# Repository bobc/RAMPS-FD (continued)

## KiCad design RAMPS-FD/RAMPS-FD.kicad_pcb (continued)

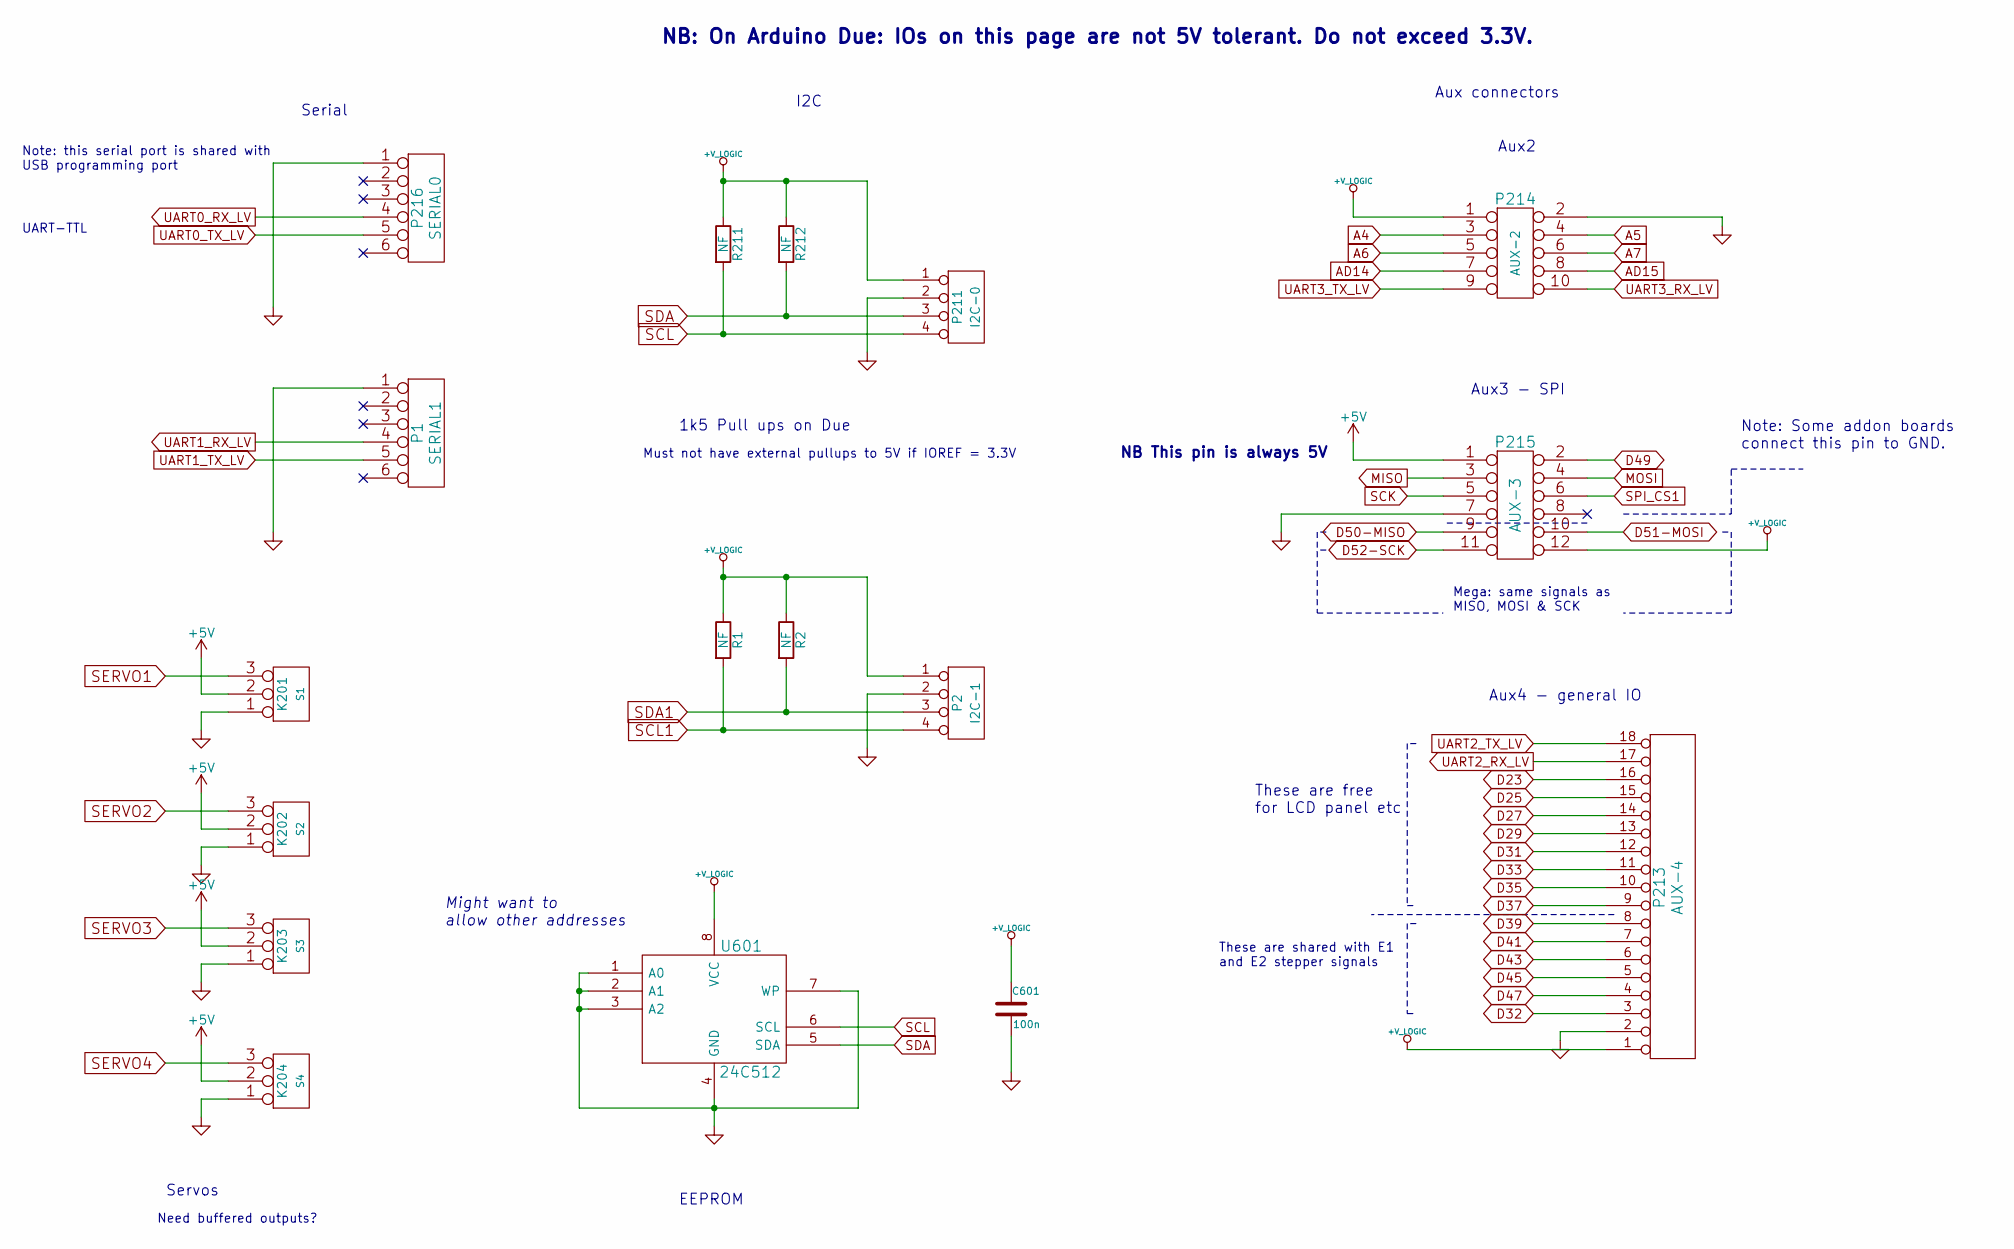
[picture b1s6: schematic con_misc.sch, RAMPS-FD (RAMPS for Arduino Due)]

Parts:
C601: 100n; C_0603
K201: S1; Pin_Header_Straight_1x03_Pitch2.54mm
K202: S2; Pin_Header_Straight_1x03_Pitch2.54mm
K203: S3; Pin_Header_Straight_1x03_Pitch2.54mm
K204: S4; Pin_Header_Straight_1x03_Pitch2.54mm
P1: SERIAL1; Pin_Header_Straight_1x06_Pitch2.54mm
P2: I2C-1; Pin_Header_Straight_1x04_Pitch2.54mm
P211: I2C-0; Pin_Header_Straight_1x04_Pitch2.54mm
P213: AUX-4; Pin_Header_Straight_1x18_Pitch2.54mm
P214: AUX-2; PIN_ARRAY_5x2_RMC
P215: AUX-3; PIN_ARRAY_6x2_RMC
P216: SERIAL0; Pin_Header_Straight_1x06_Pitch2.54mm
R1, R2, R211, R212: NF; R_0603
U601: 24C512; SO8E

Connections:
+5V: K201.2 (PM), K202.2 (PM), K203.2 (PM), K204.2 (PM), P215.1; also elsewhere on the board
+V_LOGIC: C601.1, P2.1, P211.1, P213.1, P214.1, P215.12, R1.1, R2.1, R211.1, R212.1, U601.8 (VCC); also elsewhere on the board
A4: P214.3; also elsewhere on the board
A5: P214.4; also elsewhere on the board
A6: P214.5; also elsewhere on the board
A7: P214.6; also elsewhere on the board
AD14: P214.7; also elsewhere on the board
AD15: P214.8; also elsewhere on the board
D23: P213.16; also elsewhere on the board
D25: P213.15; also elsewhere on the board
D27: P213.14; also elsewhere on the board
D29: P213.13; also elsewhere on the board
D31: P213.12; also elsewhere on the board
D32: P213.3; also elsewhere on the board
D33: P213.11; also elsewhere on the board
D35: P213.10; also elsewhere on the board
D37: P213.9; also elsewhere on the board
D39: P213.8; also elsewhere on the board
D41: P213.7; also elsewhere on the board
D43: P213.6; also elsewhere on the board
D45: P213.5; also elsewhere on the board
D47: P213.4; also elsewhere on the board
D49: P215.2; also elsewhere on the board
D50-MISO: P215.9; also elsewhere on the board
D51-MOSI: P215.10; also elsewhere on the board
D52-SCK: P215.11; also elsewhere on the board
GND: C601.2, K201.1, K202.1, K203.1, K204.1, P1.1, P2.2, P211.2, P213.2, P214.2, P215.7, P216.1, U601.1 (A0), U601.2 (A1), U601.3 (A2), U601.4 (GND), U601.7 (WP); also elsewhere on the board
MISO: P215.3; also elsewhere on the board
MOSI: P215.4; also elsewhere on the board
SCK: P215.5; also elsewhere on the board
SCL: P211.4, R211.2, U601.6 (SCL); also elsewhere on the board
SCL1: P2.4, R1.2; also elsewhere on the board
SDA: P211.3, R212.2, U601.5 (SDA); also elsewhere on the board
SDA1: P2.3, R2.2; also elsewhere on the board
SERVO1: K201.3; also elsewhere on the board
SERVO2: K202.3; also elsewhere on the board
SERVO3: K203.3; also elsewhere on the board
SERVO4: K204.3; also elsewhere on the board
SPI_CS1: P215.6; also elsewhere on the board
UART0_RX_LV: P216.4; also elsewhere on the board
UART0_TX_LV: P216.5; also elsewhere on the board
UART1_RX_LV: P1.4; also elsewhere on the board
UART1_TX_LV: P1.5; also elsewhere on the board
UART2_RX_LV: P213.17; also elsewhere on the board
UART2_TX_LV: P213.18; also elsewhere on the board
UART3_RX_LV: P214.10; also elsewhere on the board
UART3_TX_LV: P214.9; also elsewhere on the board

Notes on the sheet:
Serial
UART-TTL
Need buffered outputs?
Must not have external pullups to 5V if IOREF = 3.3V
1k5 Pull ups on Due
Aux4 - general IO
Aux3 - SPI
Aux2
Aux connectors
Servos
I2C
NB: On Arduino Due: IOs on this page are not 5V tolerant. Do not exceed 3.3V.
Note: this serial port is shared with USB programming port
These are shared with E1 and E2 stepper signals
Mega: same signals as MISO, MOSI & SCK
NB This pin is always 5V
These are free for LCD panel etc
Note: Some addon boards connect this pin to GND.
EEPROM
Might want to allow other addresses

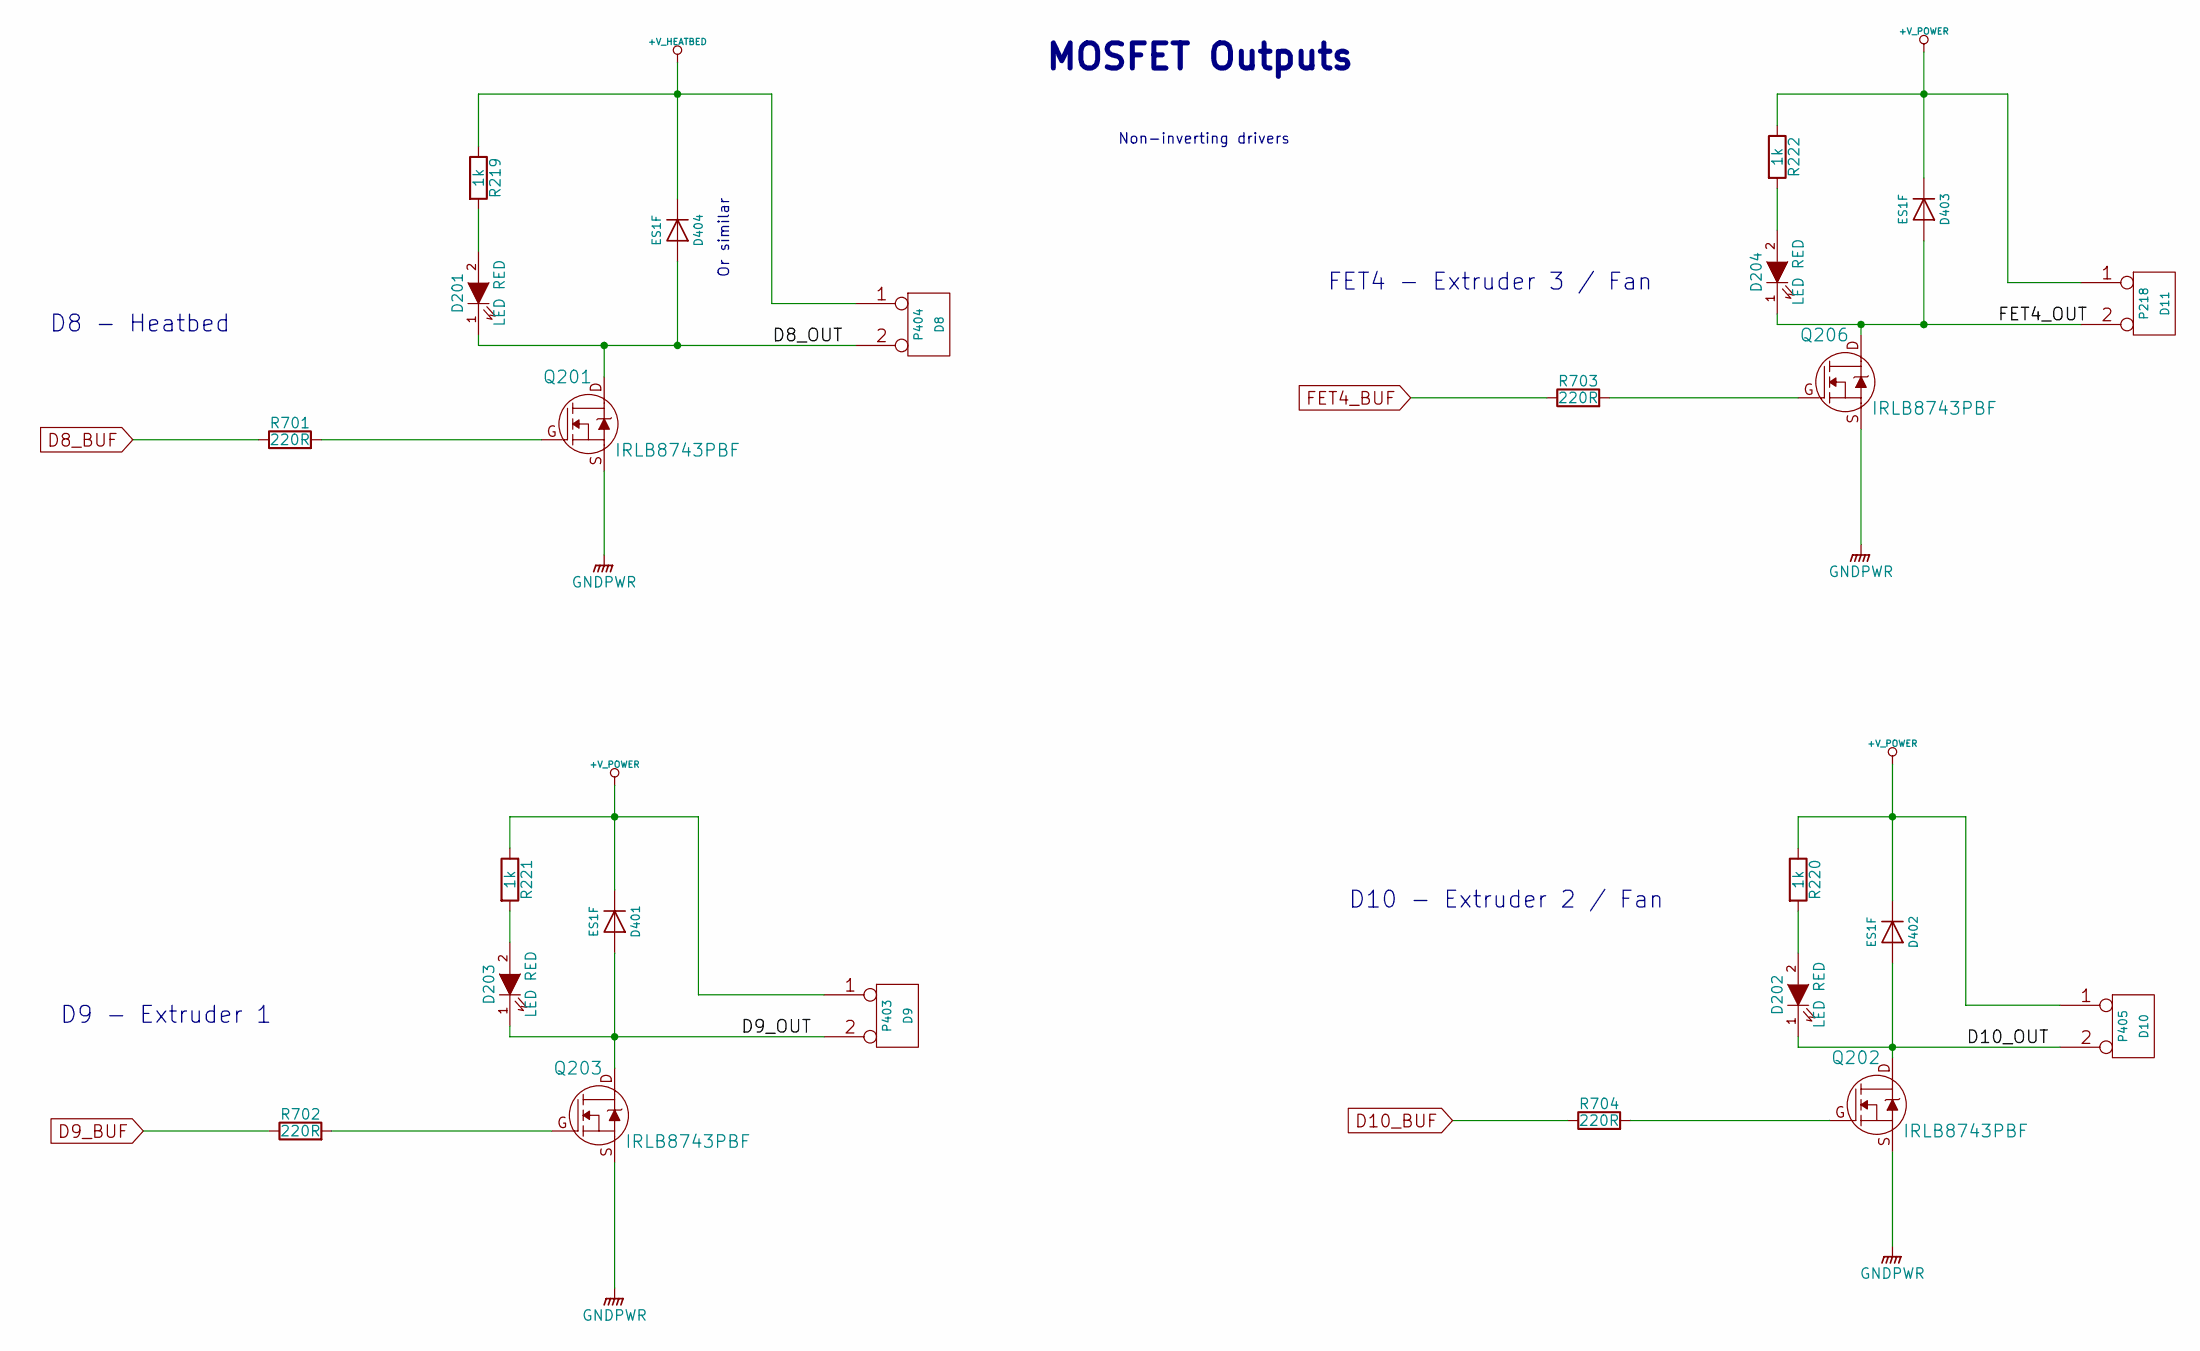
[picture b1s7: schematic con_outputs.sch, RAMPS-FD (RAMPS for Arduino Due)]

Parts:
D201, D202, D203, D204: LED RED; LED-0805_RED
D401, D402, D403, D404: ES1F; DO-214AC
P218: D11; RMC-pt_1,5-2-3,5-h
P403: D9; RMC-pt_1,5-2-3,5-h
P404: D8; mors_2p
P405: D10; RMC-pt_1,5-2-3,5-h
Q201, Q202, Q203, Q206: IRLB8743PBF; TO-220AB_IRF2804_RMC
R219, R220, R221, R222: 1k; R_0603
R701, R702, R703, R704: 220R; R_0603

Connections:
+V_HEATBED: D404.1 (K), P404.1, R219.1; also elsewhere on the board
+V_POWER: D401.1 (K), D402.1 (K), D403.1 (K), P218.1, P403.1, P405.1, R220.1, R221.1, R222.1; also elsewhere on the board
/Mosfet Outputs/D8_OUT: D201.1 (K), D404.2 (A), P404.2 (PM), Q201.D
/Mosfet Outputs/D9_OUT: D203.1 (K), D401.2 (A), P403.2 (PM), Q203.D
/Mosfet Outputs/D10_OUT: D202.1 (K), D402.2 (A), P405.2 (PM), Q202.D
/Mosfet Outputs/FET4_OUT: D204.1 (K), D403.2 (A), P218.2 (PM), Q206.D
D8_BUF: R701.1; also elsewhere on the board
D9_BUF: R702.1; also elsewhere on the board
D10_BUF: R704.1; also elsewhere on the board
FET4_BUF: R703.1; also elsewhere on the board
MOT_GND: Q201.S, Q202.S, Q203.S, Q206.S; also elsewhere on the board
unnamed: D201.2 (A), R219.2
unnamed: D202.2 (A), R220.2
unnamed: D203.2 (A), R221.2
unnamed: D204.2 (A), R222.2
unnamed: Q201.G, R701.2
unnamed: Q202.G, R704.2
unnamed: Q203.G, R702.2
unnamed: Q206.G, R703.2

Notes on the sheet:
FET4 - Extruder 3 / Fan
D10 - Extruder 2 / Fan
D9 - Extruder 1
D8 - Heatbed
Non-inverting drivers
MOSFET Outputs
Or similar

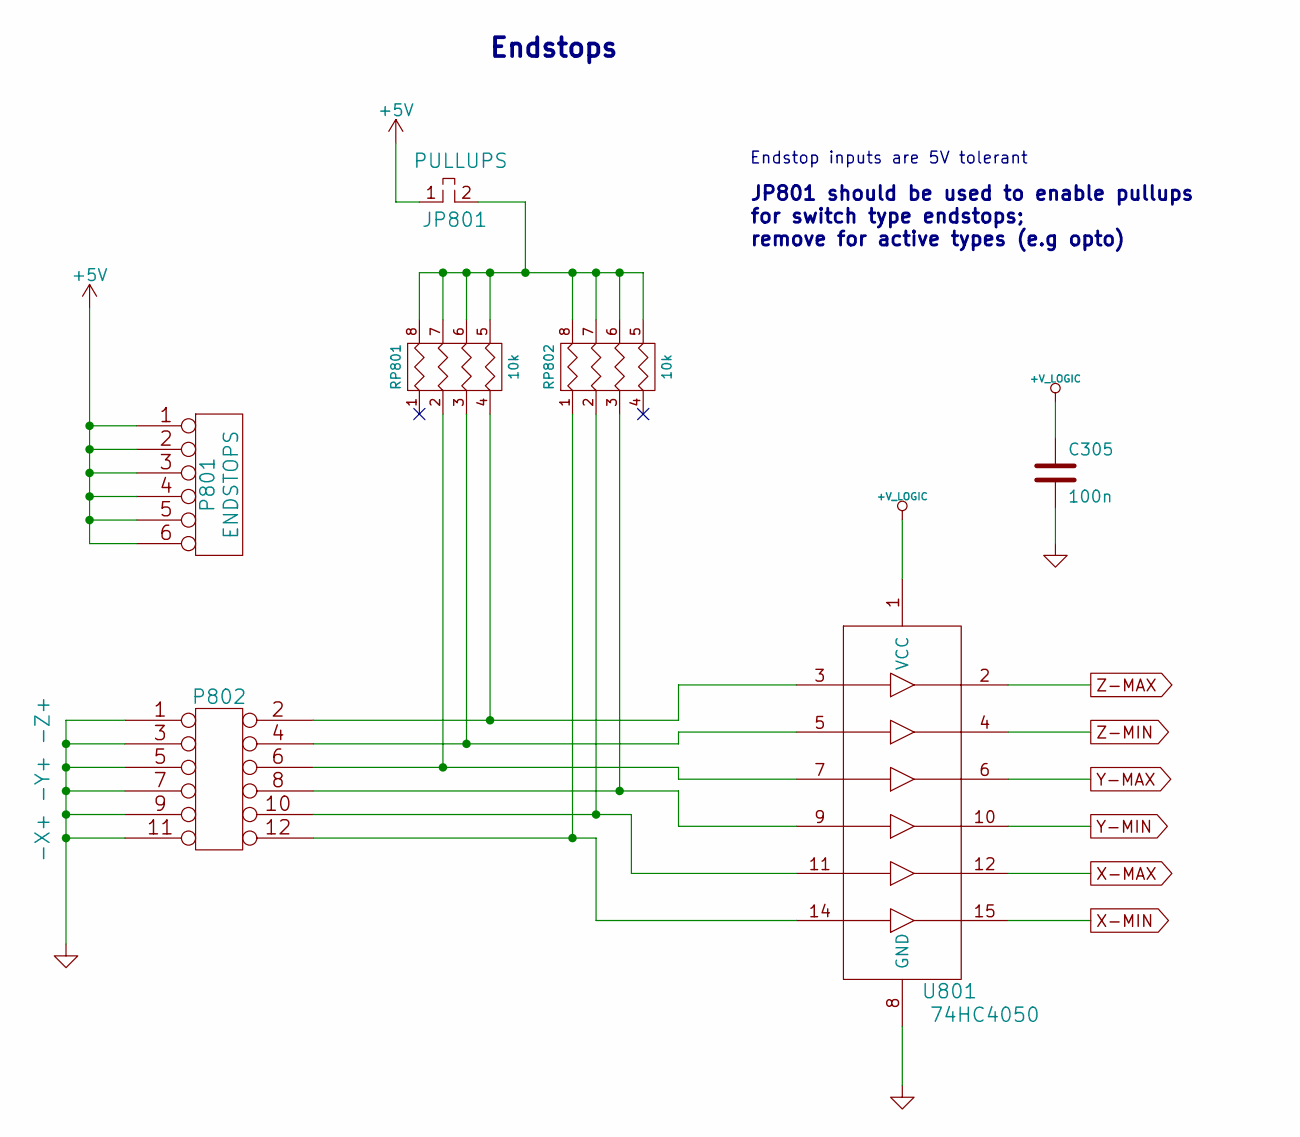
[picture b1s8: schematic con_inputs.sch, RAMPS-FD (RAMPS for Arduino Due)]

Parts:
C305: 100n; C_0603
JP801: PULLUPS; Pin_Header_Straight_1x02_Pitch2.54mm
P801: ENDSTOPS; Pin_Header_Straight_1x06_Pitch2.54mm
P802: -X+ -Y+ -Z+; Pin_Header_Straight_2x06_Pitch2.54mm
RP801, RP802: 10k; R_Cat16-4
U801: 74HC4050; TSSOP-16_4.4x5mm_Pitch0.65mm

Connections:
+5V: JP801.1, P801.1, P801.2, P801.3, P801.4, P801.5, P801.6; also elsewhere on the board
+V_LOGIC: C305.1, U801.1 (VCC); also elsewhere on the board
GND: C305.2, P802.1, P802.3, P802.5, P802.7, P802.9, P802.11, U801.8 (GND); also elsewhere on the board
unnamed: JP801.2, RP801.5 (R4), RP801.6 (R3), RP801.7 (R2), RP801.8 (R1), RP802.5 (R4), RP802.6 (R3), RP802.7 (R2), RP802.8 (R1)
unnamed: P802.2, RP801.4, U801.3
unnamed: P802.4, RP801.3, U801.5
unnamed: P802.6, RP801.2, U801.7
unnamed: P802.8, RP802.3, U801.9
unnamed: P802.10, RP802.2, U801.11
unnamed: P802.12, RP802.1, U801.14
X-MAX: U801.12; also elsewhere on the board
X-MIN: U801.15; also elsewhere on the board
Y-MAX: U801.6; also elsewhere on the board
Y-MIN: U801.10; also elsewhere on the board
Z-MAX: U801.2; also elsewhere on the board
Z-MIN: U801.4; also elsewhere on the board

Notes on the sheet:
Endstop inputs are 5V tolerant
Endstops
JP801 should be used to enable pullups for switch type endstops; remove for active types (e.g opto)

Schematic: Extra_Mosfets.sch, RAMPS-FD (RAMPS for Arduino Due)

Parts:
D901, D902: LED RED; LED-0805_RED
D903, D904: ES1F; DO-214AC
P901: D12; CONN_KK_2.54_2W
P902: D2; CONN_KK_2.54_2W
Q901, Q902: DMN2075U; SOT23GDS
R901, R902: 220R; R_0603
R905, R906: 1k; R_0603

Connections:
+12P: D903.1 (K), D904.1 (K), P901.1, P902.1, R905.1, R906.1; also elsewhere on the board
/Extra MOSFETs/P_FET5: D901.1 (K), D903.2 (A), P901.2 (PM), Q901.D
/Extra MOSFETs/P_FET6: D902.1 (K), D904.2 (A), P902.2 (PM), Q902.D
FET5_BUF: R902.1; also elsewhere on the board
FET6_BUF: R901.1; also elsewhere on the board
MOT_GND: Q901.S, Q902.S; also elsewhere on the board
unnamed: D901.2 (A), R905.2
unnamed: D902.2 (A), R906.2
unnamed: Q901.G, R902.2
unnamed: Q902.G, R901.2

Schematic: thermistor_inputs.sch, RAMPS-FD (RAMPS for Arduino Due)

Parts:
C301, C302, C303, C501: 10u; C_0603
C502, C503, C504, C505: 100n; C_0603
L1: FB; R_0603
P301: THERMISTORS; Pin_Header_Straight_2x04_Pitch2.54mm
R301, R302, R303, R501: 1k; R_0603

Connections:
+V_LOGIC: L1.1; also elsewhere on the board
AREF: L1.2, R301.1, R302.1, R303.1, R501.1
GNDA: C301.2, C302.2, C303.2, C501.2, C502.2, C503.2, C504.2, C505.2, P301.1, P301.3, P301.5, P301.7; also elsewhere on the board
THERM0: C301.1, C504.1, P301.2, R301.2; also elsewhere on the board
THERM1: C302.1, C505.1, P301.4, R302.2; also elsewhere on the board
THERM2: C303.1, C503.1, P301.6, R303.2; also elsewhere on the board
THERM3: C501.1, C502.1, P301.8, R501.2; also elsewhere on the board

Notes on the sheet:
To CPU
From thermistors
Thermistor Inputs

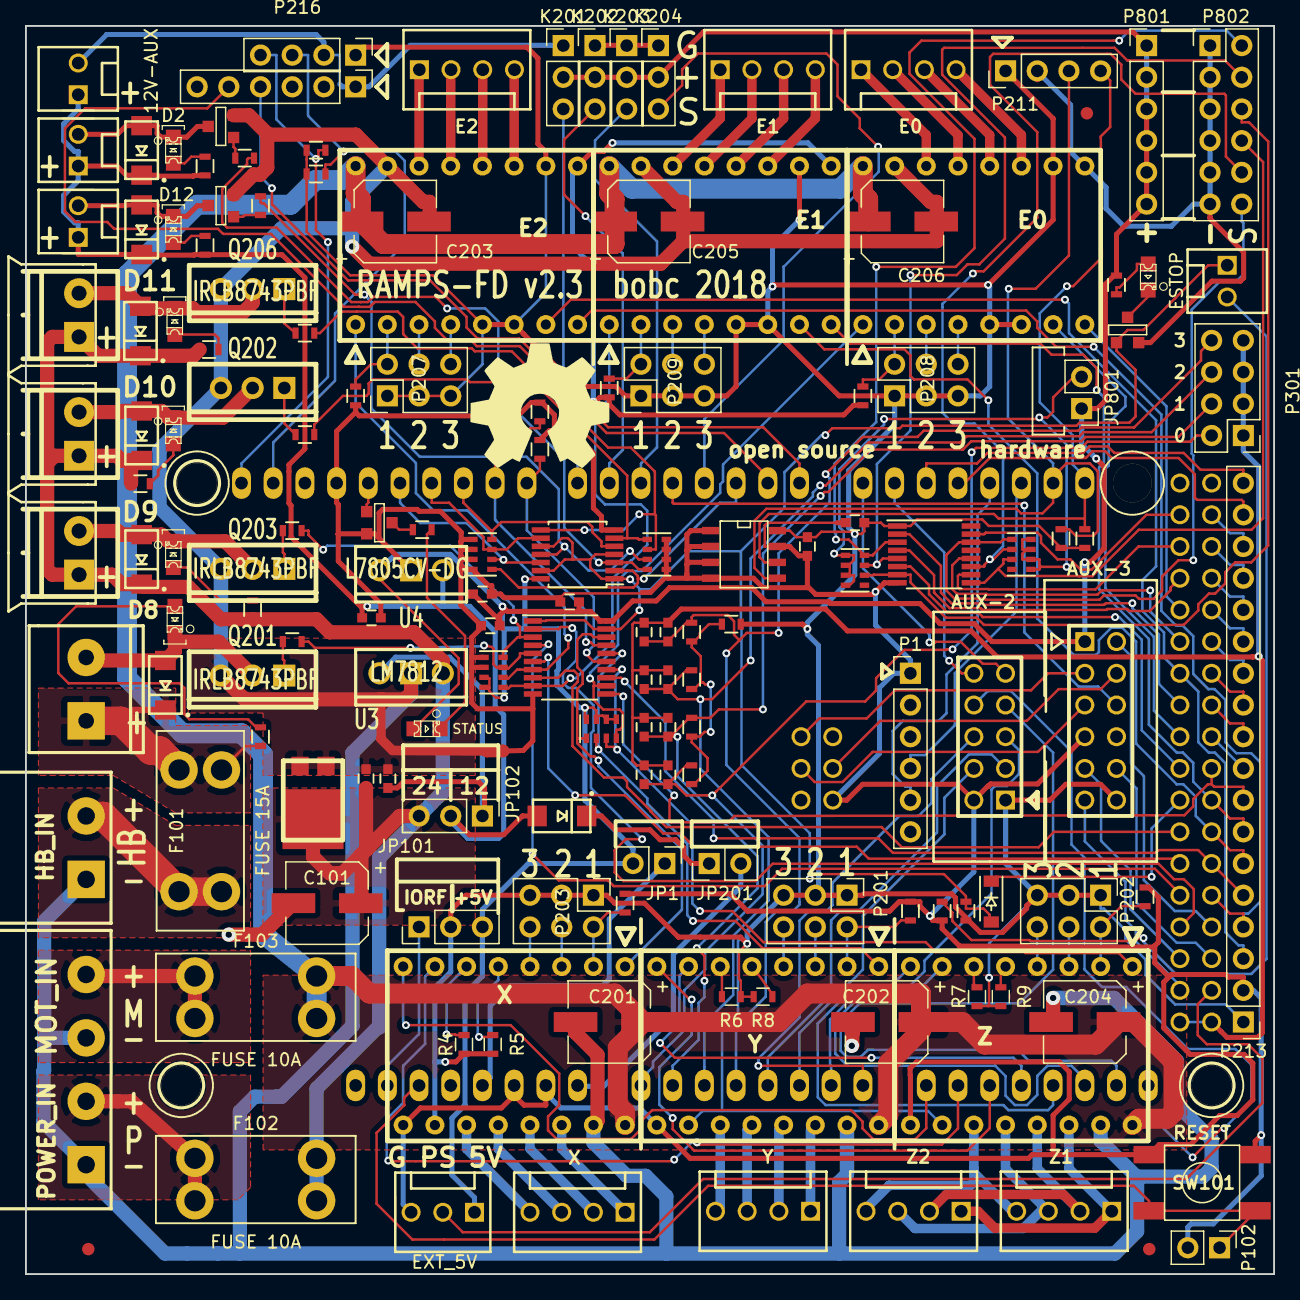
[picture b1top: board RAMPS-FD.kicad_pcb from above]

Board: 2 copper layers, 100.0 x 100.0 mm, 159 parts (0 on the bottom side), 185 nets.

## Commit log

2016-07-17 Fix readme.
2016-07-17 Initial v2.2
2018-06-01 Changed fuse holders to Keystone 3568; specificy HCT instead of ACT logic
2018-06-01 Add footprint libraries
2018-06-01 More up to date BOM for 2.2
2018-06-02 Fix 3d view; remove faulty ADC protection
